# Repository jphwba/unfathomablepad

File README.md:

# Unfathomablepad

Unfathomably bad design pcb

### Macropad Render

### Case

### PCB Layout

### Schematic

---

## Bill of Materials

| Qty | Component
| :---: | :--- |
| **1x** | Seeeduino XIAO | 
| **6x** | Diodes | 1N4148 |
| **6x** | Mechanical Switches | 
| **1x** | Rotary Encoder
| **1x** | OLED Display
| **1x** | 3D-Printed Case PA 12 Nylon (PA 603-CF)
| **1x** | PCB (See Screenshot below)||

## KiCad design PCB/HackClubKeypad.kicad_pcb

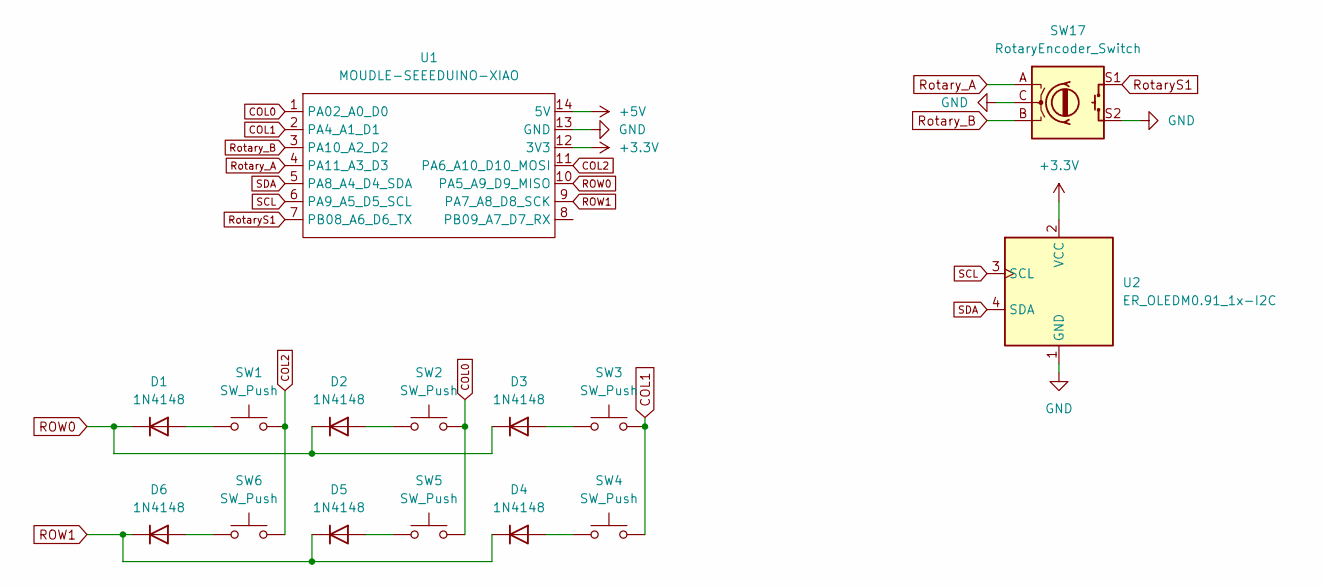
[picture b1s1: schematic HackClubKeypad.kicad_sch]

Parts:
D1, D2, D3, D4, D5, D6: 1N4148; D_DO-35_SOD27_P7.62mm_Horizontal
SW1, SW2, SW3, SW4, SW5, SW6: SW_Push; SW_Cherry_MX_1.00u_PCB
SW17: RotaryEncoder_Switch; RotaryEncoder_Alps_EC11E-Switch_Vertical_H20mm
U1: MOUDLE-SEEEDUINO-XIAO; XIAO-Generic-Hybrid-14P-2.54-21X17.8MM
U2: ER_OLEDM0.91_1x-I2C

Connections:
+3.3V: U1.12 (3V3), U2.2 (VCC)
+5V: U1.14 (5V)
COL0: SW2.1, SW5.1, U1.1 (PA02_A0_D0)
COL1: SW3.1, SW4.1, U1.2 (PA4_A1_D1)
COL2: SW1.1, SW6.1, U1.11 (PA6_A10_D10_MOSI)
GND: SW17.C, SW17.S2, U1.13 (GND), U2.1 (GND)
unnamed: D1.2 (A), SW1.2
unnamed: D2.2 (A), SW2.2
unnamed: D3.2 (A), SW3.2
unnamed: D4.2 (A), SW4.2
unnamed: D5.2 (A), SW5.2
unnamed: D6.2 (A), SW6.2
ROW0: D1.1 (K), D2.1 (K), D3.1 (K), U1.10 (PA5_A9_D9_MISO)
ROW1: D4.1 (K), D5.1 (K), D6.1 (K), U1.9 (PA7_A8_D8_SCK)
RotaryS1: SW17.S1, U1.7 (PB08_A6_D6_TX)
Rotary_A: SW17.A, U1.4 (PA11_A3_D3)
Rotary_B: SW17.B, U1.3 (PA10_A2_D2)
SCL: U1.6 (PA9_A5_D5_SCL), U2.3 (SCL)
SDA: U1.5 (PA8_A4_D4_SDA), U2.4 (SDA)

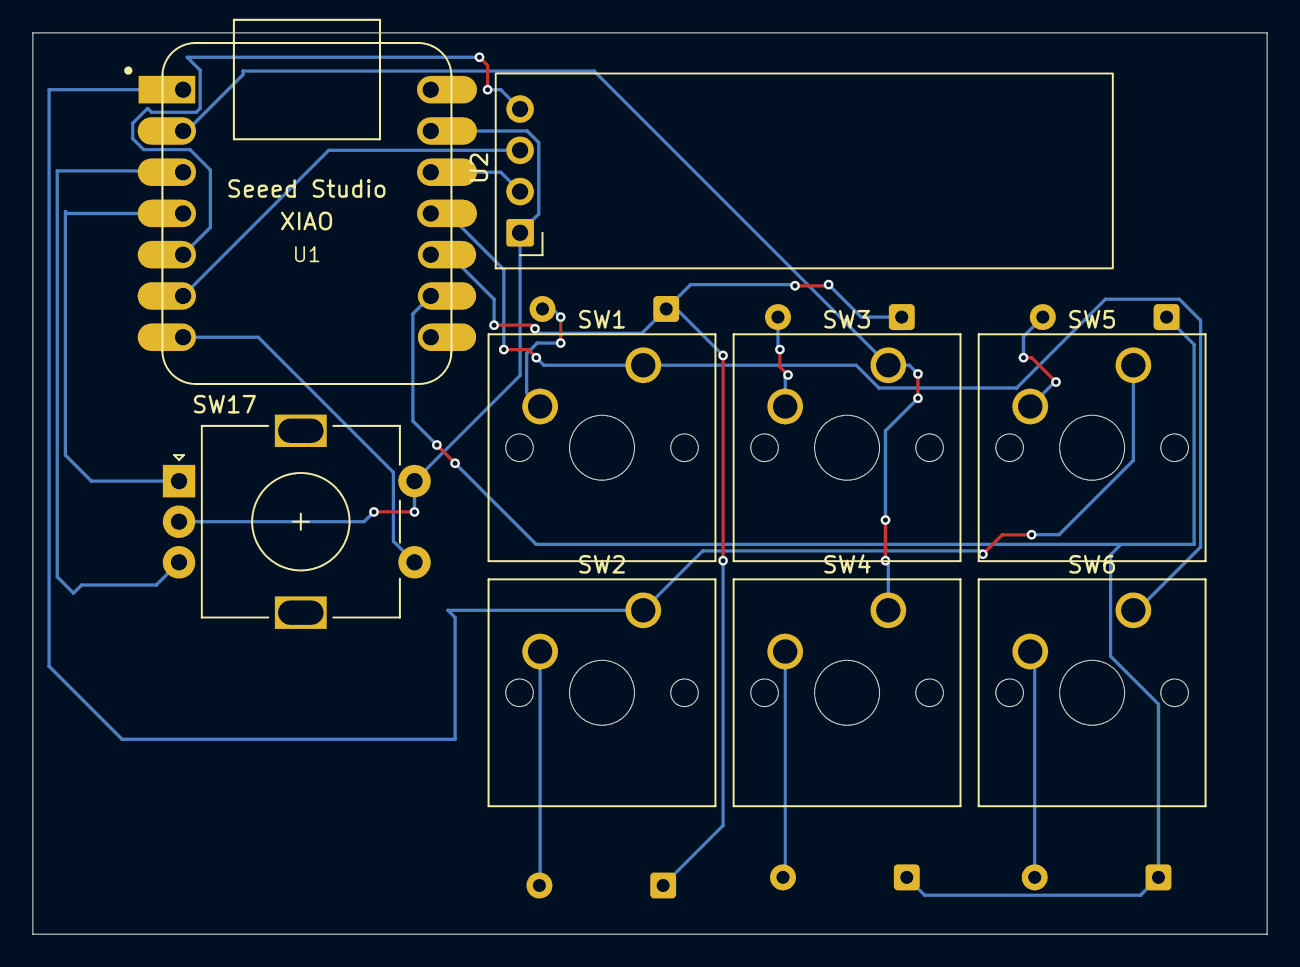
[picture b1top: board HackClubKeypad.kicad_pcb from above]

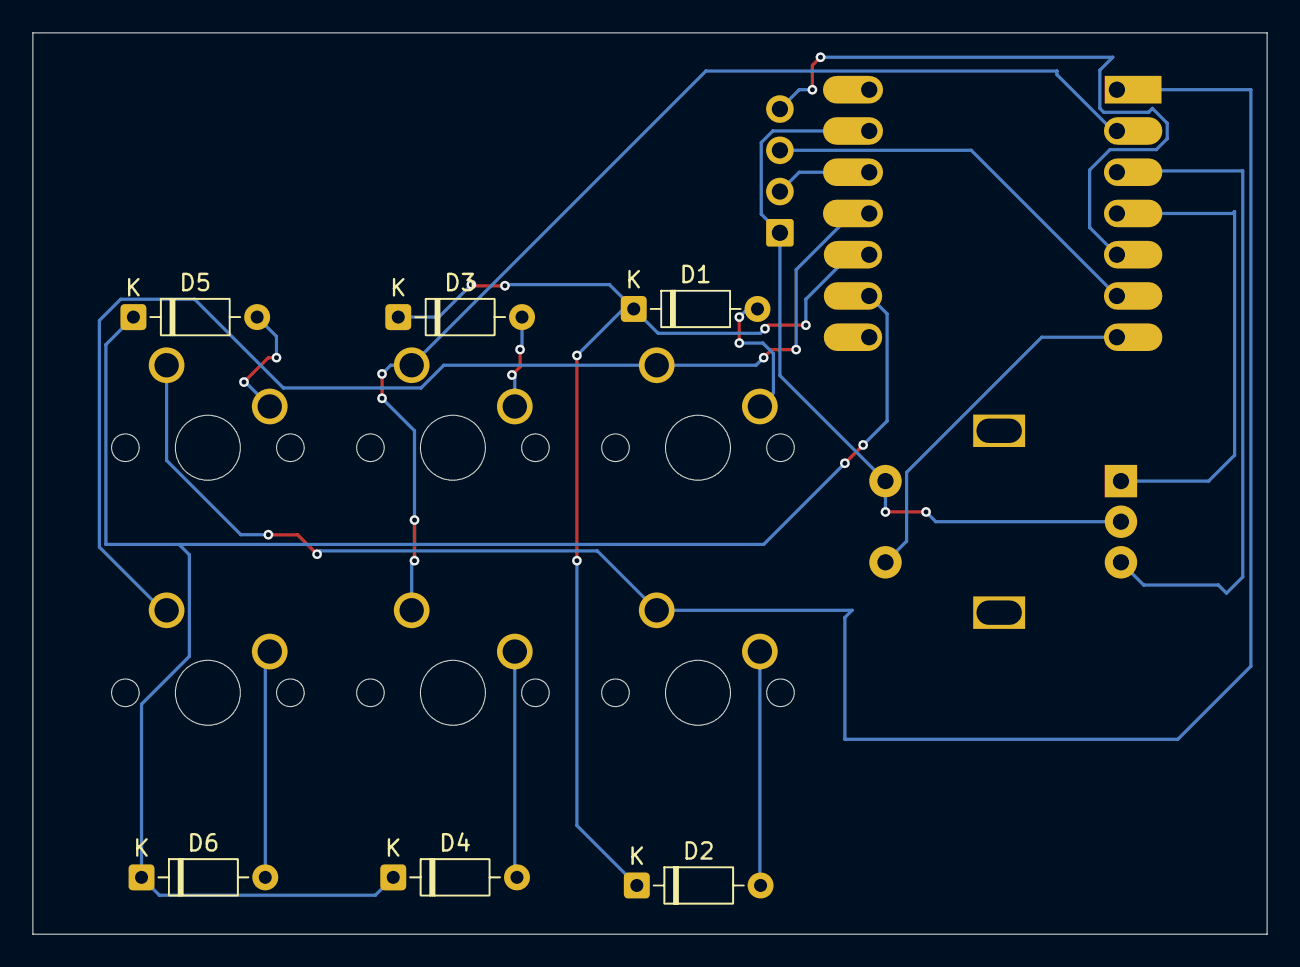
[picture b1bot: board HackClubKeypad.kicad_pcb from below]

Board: 2 copper layers, 76.0 x 55.5 mm, 15 parts (6 on the bottom side), 18 nets.

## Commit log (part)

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2026-06-19 Added all submission files
2026-06-19 Updated Cad models and added full render
2026-06-28 Update BOM
